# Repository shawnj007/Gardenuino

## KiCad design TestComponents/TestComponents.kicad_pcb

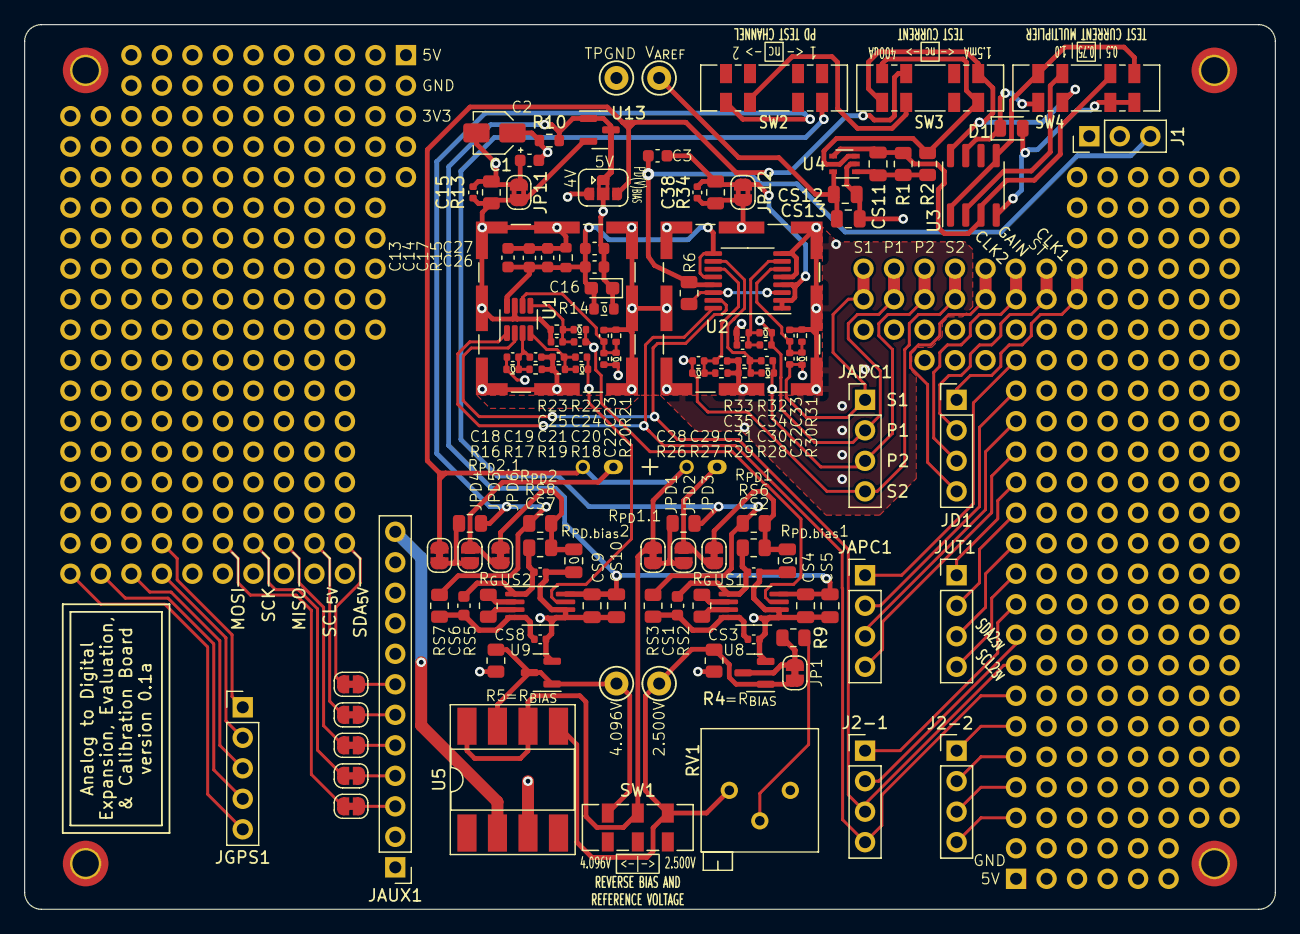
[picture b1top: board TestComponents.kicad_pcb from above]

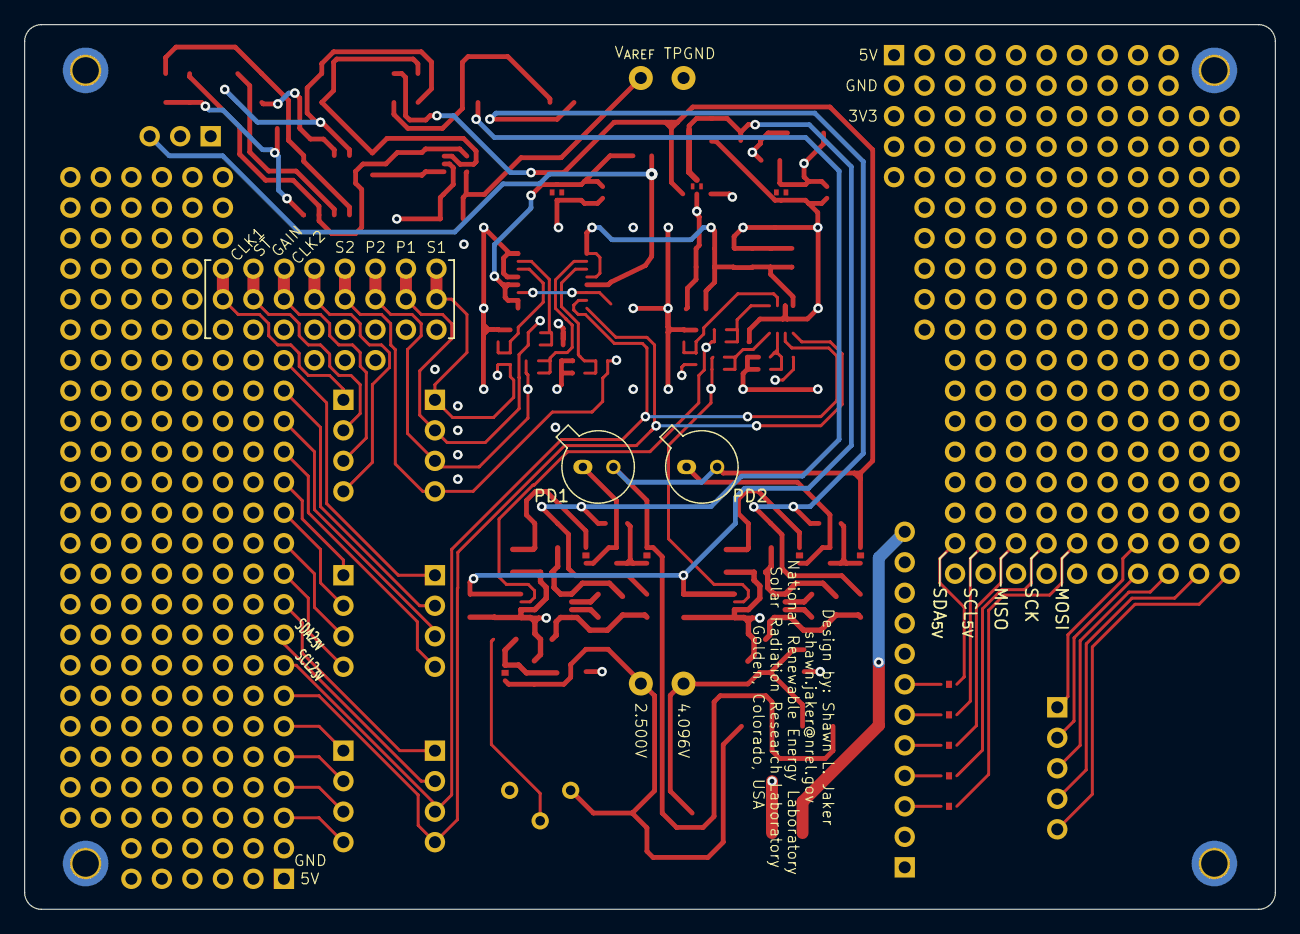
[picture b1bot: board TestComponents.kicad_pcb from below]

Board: 4 copper layers, 104.1 x 73.7 mm, 133 parts (2 on the bottom side), 86 nets.

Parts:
B1: Conn_02x20_Top_Bottom; PinHeader_CornerB1
B2: Conn_02x20_Top_Bottom; PinHeader_CornerB2
C1, C3, C14, C27: 0.1uF; C_0603_1608Metric
C2: 10uF; CP_Elec_3x5.4
C13: 10uF; C_0603_1608Metric
C15, C38: 2.5pF; C_0402_1005Metric
C16: X; CP_EIA-2012-15_AVX-P
C17: X; C_0603_1608Metric
C18, C19, C20, C21, C22, C23, C24, C25, C28, C29, C30, C31, C32, C33, C34, C35: X; C_0402_1005Metric
C26: 1pF; C_0603_1608Metric
CS1, CS6: 11.1pF; C_0603_1608Metric
CS2, CS3, CS7, CS8: 1.11pF; C_0402_1005Metric
CS4, CS9, CS12: 10uF; C_0805_2012Metric
CS5, CS10, CS11, CS13: 0.1uF; C_0805_2012Metric
D1: D_Small; D_0805_2012Metric
H1, H2, H3, H4: MountingHole; MountingHole_2.2mm_M2_ISO14580_Pad_TopBottom
J1: Conn_01x03_Socket; PinHeader_1x03_P2.54mm_Vertical
J2-1, J2-2: Conn_01x04_Male; PinHeader_1x04_P2.54mm_Vertical
J5, J6: RFShield_OnePiece; Laird_Technologies_BMI-S-101_13.66x12.70mm
JADC1: Conn_01x04_Male; PinHeader_1x04_P2.54mm_Vertical
JAPC1: Conn_01x04_Male; PinHeader_1x04_P2.54mm_Vertical
JAUX1: AUX; PinHeader_1x12_P2.54mm_Vertical
JD1: Conn_01x04_Male; PinHeader_1x04_P2.54mm_Vertical
JGPS1: GPS; PinHeader_1x05_P2.54mm_Vertical
JMISO5: SolderJumper_2_Bridged; SolderJumper-2_P1.3mm_Bridged_RoundedPad1.0x1.5mm
JMOSI5: SolderJumper_2_Bridged; SolderJumper-2_P1.3mm_Bridged_RoundedPad1.0x1.5mm
JP1: SolderJumper_2_Bridged; SolderJumper-2_P1.3mm_Bridged_RoundedPad1.0x1.5mm
JP11, JP12: SolderJumper_2_Bridged; SolderJumper-2_P1.3mm_Bridged2Bar_RoundedPad1.0x1.5mm
JP16: SolderJumper_3_Bridged12; SolderJumper-4_P1.3mm_Bridged2Bar12_RoundedPad
JPD1, JPD3, JPD4, JPD6: SolderJumper_2_Bridged; SolderJumper-2_P1.3mm_Bridged_RoundedPad1.0x1.5mm
JPD2, JPD5: SolderJumper_2_Open; SolderJumper-2_P1.3mm_Open_RoundedPad1.0x1.5mm
JSCK5: SolderJumper_2_Bridged; SolderJumper-2_P1.3mm_Bridged_RoundedPad1.0x1.5mm
JSCL5: SolderJumper_2_Bridged; SolderJumper-2_P1.3mm_Bridged_RoundedPad1.0x1.5mm
JSDA5: SolderJumper_2_Bridged; SolderJumper-2_P1.3mm_Bridged_RoundedPad1.0x1.5mm
JUT1: Conn_01x04_Male; PinHeader_1x04_P2.54mm_Vertical
PD1, PD2: S1336-18BK; S1336
R1, R6: 10K; R_0805_2012Metric
R2: 2K67; R_0805_2012Metric
R4: 250; R_0805_2012Metric
R5: 91; R_0805_2012Metric
R9: 470K; R_0805_2012Metric
R10: 24R9; R_0603_1608Metric
R13, R34: 2K; R_0805_2012Metric
R14: 0; R_0603_1608Metric
R15: X; R_0603_1608Metric
R16, R18, R20, R22, R26, R28, R30, R32: 0; R_0402_1005Metric
R17, R19, R21, R23, R27, R29, R31, R33: X; R_0402_1005Metric
RS2, RS5: R_{G}; R_0805_2012Metric
RS3, RS6, RS7, RS8: 330; R_0805_2012Metric
RV1: 10K; Potentiometer_Bourns_3296P_Horizontal
R_{PD.bias}1, R_{PD.bias}2: 1K; C_0805_2012Metric
R_{PD}1, R_{PD}2: 1G; R_0805_2012Metric
R_{PD}1.1, R_{PD}2.1: 1K; R_0805_2012Metric
SW1: SW_DPDT; SW_DPDT_CK_JS202011JAQN
SW2, SW3, SW4: SW_DP3T; SW_DP3T_CK_JS203011JAQN
TPGND-1: TestPoint; TestPoint_Keystone_5000-5004_Miniature
TPV1, TPV2, TPV5: TestPoint; TestPoint_Keystone_5000-5004_Miniature
U1: AD7991; SOT-23-8
U2: ADS1219; TSSOP-16_4.4x5mm_P0.65mm
U3: REF200AU; SOIC-8_3.9x4.9mm_P1.27mm
U4: MCP6L01x-xLT; SOT-353_SC-70-5
U5: LCC110; DIP-8_W8.89mm_SMDSocket_LongPads
U8: ADR5041B; SOT-23
U9: ADR5044B; SOT-23
U13: ADR5045B; SOT-23
US1, US2: AD8221; MSOP-8_3x3mm_P0.65mm

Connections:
2V5: JP1.2 (B), R4.2, RV1.1, SW1.3 (C), TPV1.1, U5.5, U8.1 (K)
3V1: B2.104, C3.2, J1.3, R6.2, U2.13 (DVDD)
4V0: JP16.3 (B), R5.2, SW1.1 (A), TPV2.1, U5.7, U9.1 (K), U9.3 (REF)
5V0: CS4.1, CS5.2, CS9.1, CS10.2, JP16.4, R10.1, U13.1 (K), U13.3 (REF), US1.8 (Vs+), US2.8 (Vs+)
5V3: B1.1, B2.1, C1.1, C2.1, J1.1, JAUX1.1, R4.1, R5.1, R10.2
-I_{const}=0.4mA: SW3.4, SW3.5, SW4.3, U3.8
-I_{const}=1.5mA: R2.1, SW3.1, SW3.8, U4.3 (+)
/InsturmentationsAmps/INV1: JPD3.2 (B), RS6.1, R_{PD.bias}1.1, R_{PD}1.2
/InsturmentationsAmps/INV2: JPD6.2 (B), RS8.1, R_{PD.bias}2.1, R_{PD}2.2
/InsturmentationsAmps/I_{C}1: D1.1 (K), SW4.4, U3.7
/InsturmentationsAmps/I_{C}1out: SW4.7, U3.2
/InsturmentationsAmps/I_{C}in: SW4.5, SW4.8, U3.1, U3.5
/InsturmentationsAmps/I_{C}out: CS11.2, R1.1, SW4.6, U3.3, U4.4 (-)
/InsturmentationsAmps/I_{Mirror}_{IN}: D1.2 (A), SW4.1, SW4.2, U3.4
/InsturmentationsAmps/PD1_{TEST}: RS3.1, R_{PD}1.1, R_{PD}1.1.2, SW2.1
/InsturmentationsAmps/PD2_{TEST}: RS7.1, R_{PD}2.1, R_{PD}2.1.2, SW2.4
/InsturmentationsAmps/PD_{TEST}: SW2.3, SW3.3
/TestConnectors/APCRX_5V: B1.125, JAPC1.2
/TestConnectors/APCTX_5V: B1.136, JAPC1.1
/TestConnectors/CAN_H_5V: B1.85, JUT1.3
/TestConnectors/CAN_L_5V: B1.77, JUT1.4
/TestConnectors/CLK1_5V: B1.164, B1.177, JD1.1
/TestConnectors/CLK2_5V: B1.161, B1.174, JD1.4
/TestConnectors/GAIN_5V: B1.162, B1.175, JD1.3
/TestConnectors/GPSRX_5V: B2.202, JGPS1.3
/TestConnectors/GPSTX_5V: B2.203, JGPS1.4
/TestConnectors/GPS_5V: B2.191, JGPS1.1
/TestConnectors/GPS_GND: B2.201, JGPS1.2
/TestConnectors/MISO_5V: JAUX1.5, JMISO5.1 (A)
/TestConnectors/MOSI_5V: JAUX1.3, JMOSI5.1 (A)
/TestConnectors/PPS_5V: B2.204, JGPS1.5
/TestConnectors/RX_5V: B1.109, JAPC1.4
/TestConnectors/SCK_5V: JAUX1.4, JSCK5.1 (A)
/TestConnectors/SCL_5V: JAUX1.6, JSCL5.1 (A)
/TestConnectors/SDA_5V: JAUX1.7, JSDA5.1 (A)
/TestConnectors/ST_5V: B1.163, B1.176, JD1.2
/TestConnectors/TX_5V: B1.117, JAPC1.3
/TestConnectors/UT1_5V: B1.101, JUT1.1
/TestConnectors/UT2_5V: B1.93, JUT1.2
GND1: B1.7, B1.199, B2.11, C1.2, C2.2, C3.1, C15.2, C38.2, CS2.2, CS3.2, CS4.2, CS5.1, CS7.2, CS8.2, CS9.2, CS10.1, CS12.2, CS13.1, JAUX1.2, JP11.1 (A), JP12.1 (A), R13.2, R34.2, RV1.3, R_{PD.bias}1.2, R_{PD.bias}2.2, TPGND-1.1, U2.1 (A0), U2.2 (A1), U2.4 (DGND), U4.2 (V-), U5.3, U8.2 (A), U9.2 (A), US1.5 (Vs-), US1.6 (Ref), US2.5 (Vs-), US2.6 (Ref)
GND_{RF}: C13.2, C14.2, C15.1, C17.2, C19.2, C21.2, C23.2, C25.2, C29.2, C31.2, C33.2, C35.2, C38.1, J5.1 (Shield), J6.1 (Shield), JP11.2 (B), JP12.2 (B), R13.1, R15.1, R17.1, R19.1, R21.1, R23.1, R27.1, R29.1, R31.1, R33.1, R34.1, U1.7 (GND), U2.5 (AGND), U2.8 (REFN), U13.2 (A)
J-1-1: B1.69, J2-1.1
J-1-2: B1.61, J2-1.2
J-1-3: B1.53, J2-1.3, U1.2 (SDA), U2.15 (SDA)
J-1-4: B1.45, J2-1.4, U1.1 (SCL), U2.16 (SCL)
J-2-1: B1.37, J2-2.1
J-2-2: B1.29, J2-2.2
J-2-3: B1.21, J2-2.3
J-2-4: B1.13, J2-2.4
unnamed: B2.185, JSDA5.2 (B)
unnamed: B2.186, JSCL5.2 (B)
unnamed: B2.187, JMISO5.2 (B)
unnamed: B2.188, JSCK5.2 (B)
unnamed: B2.189, JMOSI5.2 (B)
unnamed: CS11.1, R1.2, R2.2, U4.1
unnamed: JP1.1 (A), R9.1, U8.3 (REF)
unnamed: JPD1.2 (B), JPD2.2 (B), R_{PD}1.1.1
unnamed: JPD2.1 (A), JPD3.1 (A), PD1.1 (A)
unnamed: JPD4.2 (B), JPD5.2 (B), R_{PD}2.1.1
unnamed: JPD5.1 (A), JPD6.1 (A), PD2.1 (A)
unnamed: R9.2, RV1.2
unnamed: RS2.1, US1.3 (Rg)
unnamed: RS2.2, US1.2 (Rg)
unnamed: RS5.1, US2.3 (Rg)
unnamed: RS5.2, US2.2 (Rg)
unnamed: R6.1, U2.3 (~RESET), U2.14 (~DRDY)
unnamed: CS1.1, CS3.1, RS3.2, US1.4 (+)
unnamed: CS1.2, CS2.1, RS6.2, US1.1 (-)
unnamed: CS6.1, CS8.1, RS7.2, US2.4 (+)
unnamed: CS6.2, CS7.1, RS8.2, US2.1 (-)
P1: B1.158, B1.171, C24.1, C34.1, JADC1.2, R22.2, R32.2, US1.7
P1_{RF}: C24.2, C25.1, R22.1, R23.2, U1.5 (Vin2)
P1_{RF}-2: C34.2, C35.1, R32.1, R33.2, U2.7 (AIN2)
P2: B1.159, B1.172, C20.1, C30.1, JADC1.3, R18.2, R28.2, US2.7
P2_{RF}: C20.2, C21.1, R18.1, R19.2, U1.4 (Vin1)
P2_{RF}-2: C30.2, C31.1, R28.1, R29.2, U2.10 (AIN1)
PD(V)_{BIAS}: JP16.1 (A), JPD1.1 (A), JPD4.1 (A), PD1.2 (K), PD2.2 (K), SW1.2 (B), SW3.7, U5.6, U5.8
PWM: JAUX1.12, U5.2
S1: B1.157, B1.170, C22.1, C32.1, JADC1.1, R20.2, R30.2
S1_{RF}: C22.2, C23.1, R20.1, R21.2, U1.6 (Vin3)
S1_{RF}-2: C32.2, C33.1, R30.1, R31.2, U2.6 (AIN3)
S2: B1.160, B1.173, C18.1, C28.1, JADC1.4, R16.2, R26.2
S2_{RF}: C18.2, C19.1, R16.1, R17.2, U1.3 (Vin0)
S2_{RF}-2: C28.2, C29.1, R26.1, R27.2, U2.11 (AIN0)
V_{AREF}: C16.1, C26.1, C27.1, CS12.1, CS13.2, JP16.2 (C), R14.1, TPV5.1, U4.5 (V+)
V_{RF}: C13.1, C14.1, C16.2, C17.1, C26.2, C27.2, R14.2, R15.2, U1.8 (VDD), U2.9 (REFP), U2.12 (AVDD)

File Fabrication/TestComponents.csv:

"Source:","/home/sjaker/gits/Gardenuino/TestComponents/TestComponents.kicad_sch"
"Date:","Mon 10 Jul 2023 09:48:05 PM MDT"
"Tool:","Eeschema 6.0.2+dfsg-1"
"Generator:","/home/sjaker/gits/Gardenuino/bom_csv_grouped_by_value_with_fp_and_pn.py"
"Component Count:","105"
"Ref","Qnty","Value","Cmp name","Footprint","Description","Part Number","Vendor"
"C1, C3, C14, C27, ","4","0.1uF","C","Capacitor_SMD:C_0603_1608Metric","Unpolarized capacitor","CL05A104KA5NNNC",""
"C2, ","1","10uF","C_Polarized_Small_US","Capacitor_SMD:CP_Elec_3x5.4","Polarized capacitor, small US symbol","865090368008 ",""
"C13, ","1","10uF","C_Polarized_Small_US","Capacitor_SMD:C_0603_1608Metric","Polarized capacitor, small US symbol","F381A106MMAAH1",""
"C15, C38, ","2","2.5pF","C_Small","Capacitor_SMD:C_0402_1005Metric","Unpolarized capacitor, small symbol","CL05C2R5CB5NNNC",""
"C16, ","1","X","C_Polarized_US","Capacitor_Tantalum_SMD:CP_EIA-2012-15_AVX-P","Polarized capacitor, US symbol","",""
"C17, ","1","X","C","Capacitor_SMD:C_0603_1608Metric","Unpolarized capacitor","",""
"C18, C19, C20, C21, C22, C23, C24, C25, C28, C29, C30, C31, C32, C33, C34, C35, ","16","X","C","Capacitor_SMD:C_0402_1005Metric","Unpolarized capacitor","",""
"C26, ","1","1pF","C","Capacitor_SMD:C_0603_1608Metric","Unpolarized capacitor","CL05A104KA5NNNC",""
"CS1, CS6, ","2","11.1pF","C_Small","Capacitor_SMD:C_0603_1608Metric","Unpolarized capacitor, small symbol","06035J100FBTTR",""
"CS2, CS3, CS7, CS8, ","4","1.11pF","C_Small","Capacitor_SMD:C_0402_1005Metric","Unpolarized capacitor, small symbol","04023J1R1PBSTR",""
"CS4, CS9, CS12, ","3","10uF","C_Small","Capacitor_SMD:C_0805_2012Metric","Unpolarized capacitor, small symbol","CL21A106KACLRNC",""
"CS5, CS10, CS11, CS13, ","4","0.1uF","C_Small","Capacitor_SMD:C_0805_2012Metric","Unpolarized capacitor, small symbol","CL21B104KACNNNC",""
"J2-1, J2-2, ","2","Conn_01x04_Male","Conn_01x04_Male","Connector_PinHeader_2.54mm:PinHeader_1x04_P2.54mm_Vertical","Generic connector, single row, 01x04, script generated (kicad-library-utils/schlib/autogen/connector/)","PH1-04-UA",""
"J3V1, ","1","Conn_01x01_Male","Conn_01x01_Male","Connector_PinHeader_2.54mm:PinHeader_1x01_P2.54mm_Vertical","Generic connector, single row, 01x01, script generated (kicad-library-utils/schlib/autogen/connector/)","PH1-01-UA",""
"J5, J6, ","2","RFShield_OnePiece","RFShield_OnePiece_2","RF_Shielding:Laird_Technologies_BMI-S-101_13.66x12.70mm","One-piece EMI RF shielding cabinet","BMI-S-101",""
"JADC1, ","1","Conn_01x04_Male","Conn_01x04_Male","Connector_PinHeader_2.54mm:PinHeader_1x04_P2.54mm_Vertical","Generic connector, single row, 01x04, script generated (kicad-library-utils/schlib/autogen/connector/)","PH1-04-UA",""
"JAPC1, ","1","Conn_01x04_Male","Conn_01x04_Male","Connector_PinHeader_2.54mm:PinHeader_1x04_P2.54mm_Vertical","Generic connector, single row, 01x04, script generated (kicad-library-utils/schlib/autogen/connector/)","PH1-04-UA",""
"JAUX1, ","1","AUX","Conn_01x12_Male","Connector_PinHeader_2.54mm:PinHeader_1x12_P2.54mm_Vertical","Generic connector, single row, 01x12, script generated (kicad-library-utils/schlib/autogen/connector/)","PH1-12-UA",""
"JD1, ","1","Conn_01x04_Male","Conn_01x04_Male","Connector_PinHeader_2.54mm:PinHeader_1x04_P2.54mm_Vertical","Generic connector, single row, 01x04, script generated (kicad-library-utils/schlib/autogen/connector/)","PH1-04-UA",""
"JGPS1, ","1","GPS","Conn_01x05_Male","Connector_PinHeader_2.54mm:PinHeader_1x05_P2.54mm_Vertical","Generic connector, single row, 01x05, script generated (kicad-library-utils/schlib/autogen/connector/)","PH1-05-UA",""
"JUT1, ","1","Conn_01x04_Male","Conn_01x04_Male","Connector_PinHeader_2.54mm:PinHeader_1x04_P2.54mm_Vertical","Generic connector, single row, 01x04, script generated (kicad-library-utils/schlib/autogen/connector/)","PH1-04-UA",""
"JVIN1, ","1","Conn_01x01_Male","Conn_01x01_Male","Connector_PinHeader_2.54mm:PinHeader_1x01_P2.54mm_Vertical","Generic connector, single row, 01x01, script generated (kicad-library-utils/schlib/autogen/connector/)","PH1-01-UA",""
"R1, R6, ","2","10K","R","Resistor_SMD:R_0805_2012Metric","Resistor","ERA-6VRW1002V",""
"R2, ","1","2K67","R","Resistor_SMD:R_0805_2012Metric","Resistor","ERJ-PB6B2671V",""
"R4, ","1","402","R","Resistor_SMD:R_0805_2012Metric","Resistor","ERJ-PB6B4020V",""
"R5, ","1","200","R","Resistor_SMD:R_0805_2012Metric","Resistor","ERJ-6ENF1740V",""
"R9, ","1","470K","R","Resistor_SMD:R_0805_2012Metric","Resistor","ERJ-PB6B4703V",""
"R10, R15, ","2","X","R","Resistor_SMD:R_0603_1608Metric","Resistor","",""
"R13, R34, ","2","2K","R","Resistor_SMD:R_0805_2012Metric","Resistor","ERJ-6ENF2001V",""
"R14, ","1","0","R","Resistor_SMD:R_0603_1608Metric","Resistor","ERJ-U030R00V",""
"R16, R18, R20, R22, R26, R28, R30, R32, ","8","0","R","Resistor_SMD:R_0402_1005Metric","Resistor","ERJ-2GE0R00X",""
"R17, R19, R21, R23, R27, R29, R31, R33, ","8","X","R","Resistor_SMD:R_0402_1005Metric","Resistor","",""
"R_{C}1, ","1","500","R","Resistor_SMD:R_0805_2012Metric","Resistor","ERJ-PB6B4990V",""
"R_{PD.bias}1, R_{PD.bias}2, ","2","0","R","Capacitor_SMD:C_0805_2012Metric","Resistor","ERJ-6GEY0R00V",""
"R_{PD}1, R_{PD}2, ","2","1M","R","Resistor_SMD:R_0805_2012Metric","Resistor","ERA-6AEB105V",""
"R_{PD}1.1, ","1","2K","R","Resistor_SMD:R_0805_2012Metric","Resistor","ERJ-6ENF2001V",""
"R_{PD}2.1, ","1","2K","R","Resistor_SMD:R_0805_2012Metric","Resistor","ERJ-6ENF2001V",""
"RS2, RS5, ","2","R_{G}","R","Capacitor_SMD:C_0805_2012Metric","Resistor","",""
"RS3, RS6, RS7, RS8, ","4","330","R","Resistor_SMD:R_0805_2012Metric","Resistor","ERA-6VEB3300V",""
"RV1, ","1","10K","R_Potentiometer","Potentiometer_THT:Potentiometer_Bourns_3296P_Horizontal","Potentiometer","3296P-1-103LF",""
"SW1, SW3, ","2","SW_DPDT","SW_DPDT_x2","Gardenuino Custom:SW_DPDT_CK_JS202011JAQN","Switch, dual pole double throw, separate symbols","JS202011JAQN",""
"SW2, ","1","SW_DP3T","SW_DP3T","Gardenuino Custom:SW_DP3T_CK_JS203011JAQN","Switch, three position, dual pole triple throw, 3 position switch, SP3T","JS203011JAQN",""
"U1, ","1","AD7991","AD799x","Package_TO_SOT_SMD:SOT-23-8","","AD7991YRJZ-1500RL7",""
"U2, ","1","ADS1219","ADS1219","Package_SO:TSSOP-16_4.4x5mm_P0.65mm","Low-power, quad-input, 24-bit analog to digital converter, integrated temperature sensor, SPI interface, TSSOP-16 package","ADS1219",""
"U3, ","1","REF200AU","REF200AU","Package_SO:SOIC-8_3.9x4.9mm_P1.27mm","2x100μA Current Sources/Sinks with Current Mirror, SO-8","REF200AU",""
"U4, ","1","MCP6L01x-xLT","MCP6L01x-xLT","Package_TO_SOT_SMD:SOT-353_SC-70-5","Single, 1 MHz, Rail-to-Rail input and output, SC-70-5","MCP6L01T-E/LT",""
"U8, ","1","ADR510","ADR510_1","Package_TO_SOT_SMD:SOT-23","Shunt Regulator, SOT-23","ADR510ARTZ-REEL7",""
"U9, ","1","ADR5043BRTZ","ADR510","Package_TO_SOT_SMD:SOT-23","Shunt Regulator, SOT-23","ADR5043BRTZ",""
"U13, ","1","X","ADR510","Package_TO_SOT_SMD:SOT-23","Shunt Regulator, SOT-23","",""
"US1, US2, ","2","AD8221","AD8236","Package_SO:MSOP-8_3x3mm_P0.65mm","Single 40 μA Micropower Instrumentation Amplifier with Zero Crossover Distortion, MSOP-8","AD8221ARMZ",""

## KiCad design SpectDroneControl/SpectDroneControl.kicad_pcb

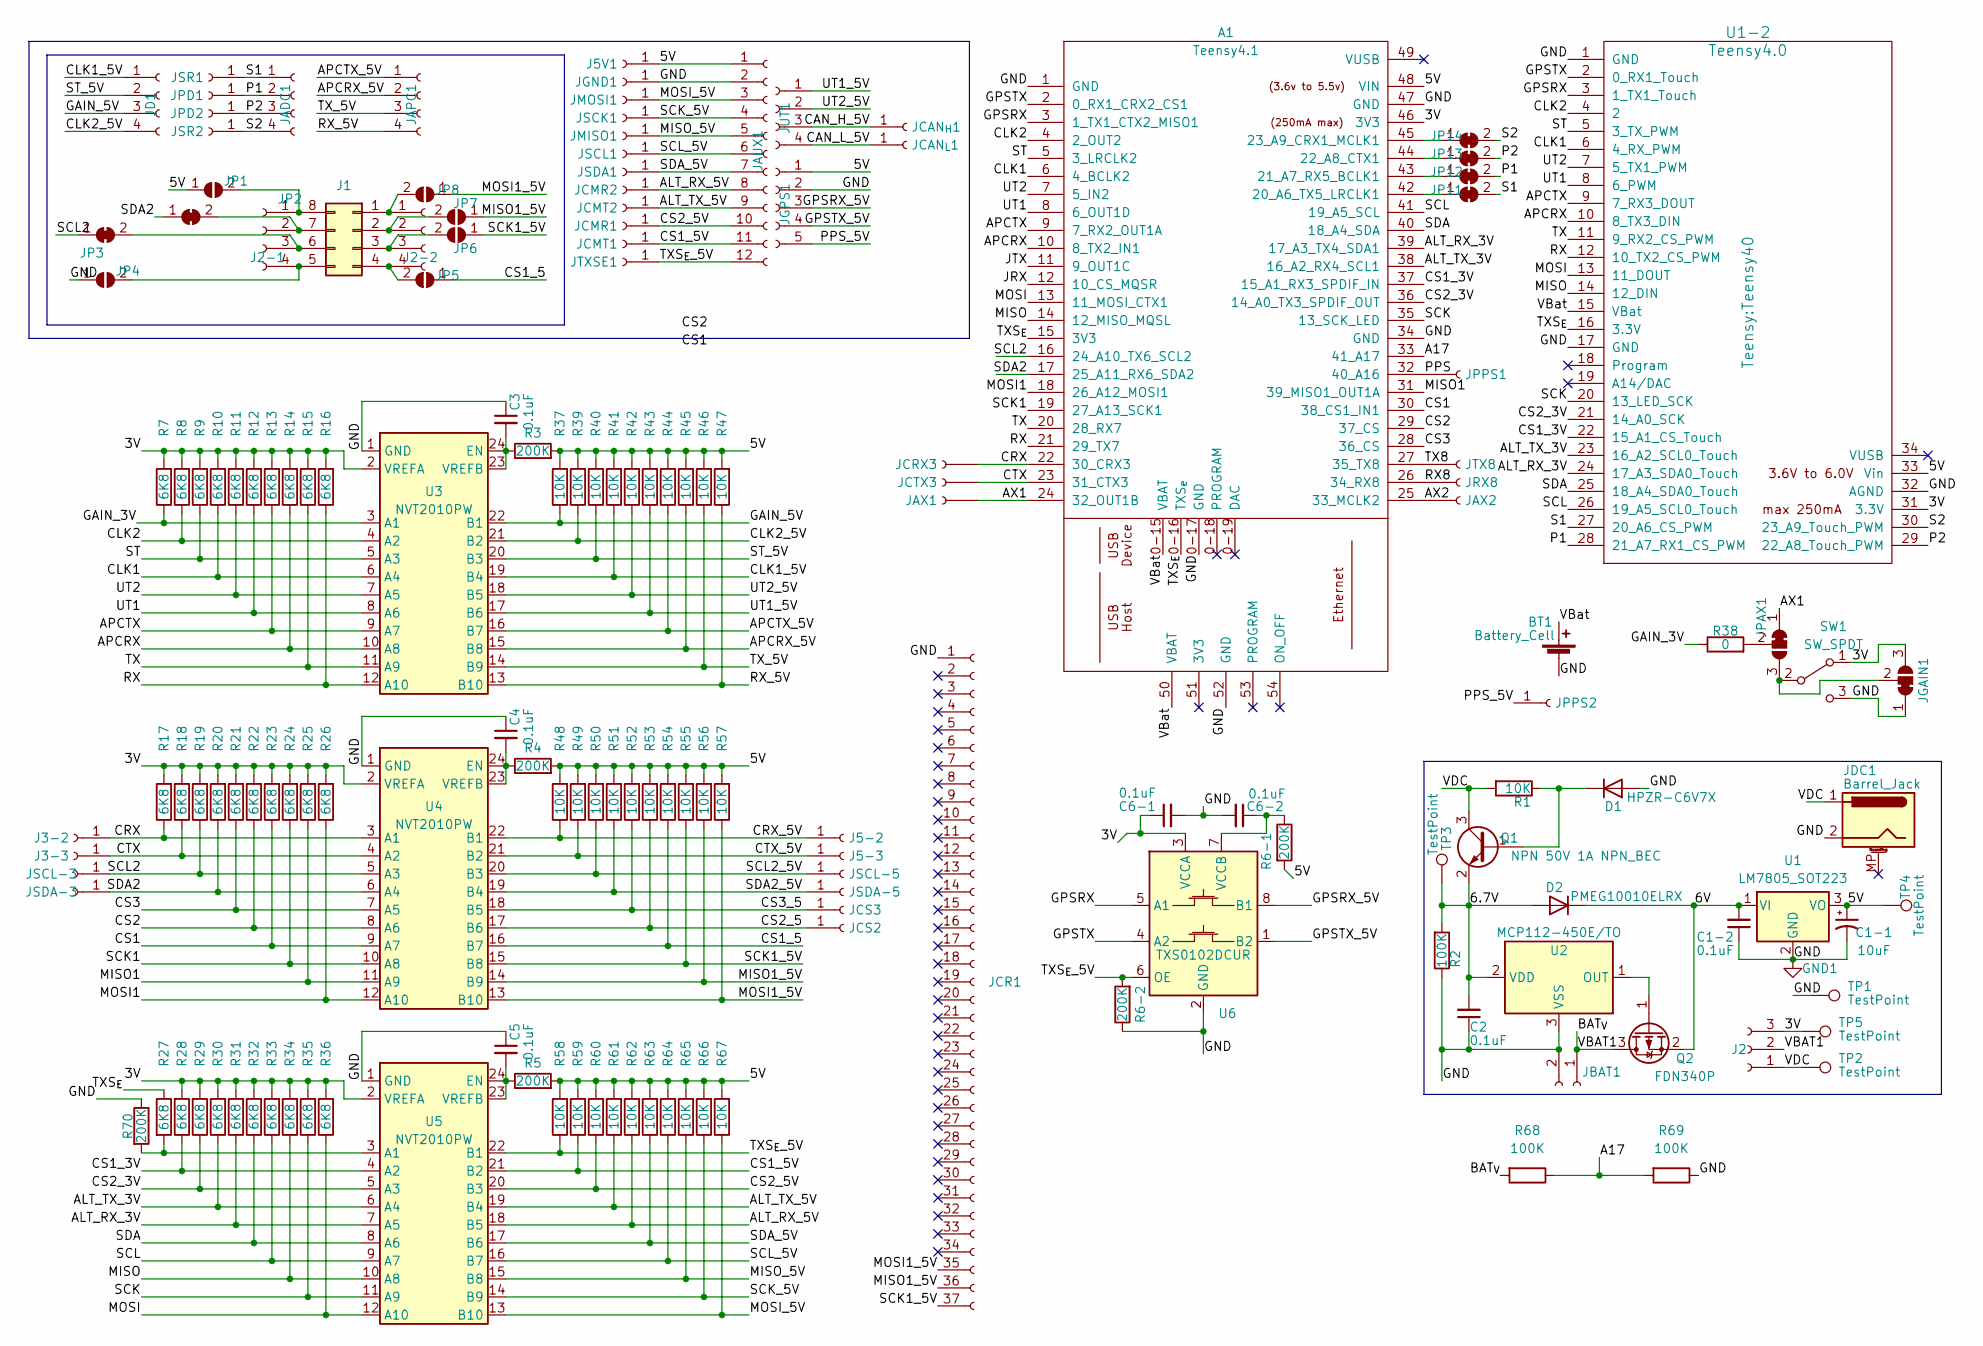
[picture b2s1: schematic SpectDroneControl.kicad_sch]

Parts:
A1: Teensy4.1; Teensy4.0-1
BT1: Battery_Cell; BatteryHolder_Keystone_3000_1x12mm; Part Number 3000
C1-1: 10uF; CP_Elec_3x5.4; Part Number 865090368008
C1-2, C2, C3, C4, C5, C6-1, C6-2: 0.1uF; C_0805_2012Metric; Part Number CL21B104KACNNNC
D1: D; D_SOD-123F; Part Number HPZR-C6V7X
D2: D; Nexperia_CFP3_SOD-123W; Part Number PMEG10010ELRX
J1: Conn_02x03_Counter_Clockwise; PinSocket_2x04_P2.54mm_Vertical_renumber; Part Number RS2-08-G
J2: Conn_01x03_Socket; PinSocket_1x03_P2.54mm_Vertical
J2-1, J2-2: Conn_01x04_Female; PinSocket_1x04_P2.54mm_Vertical; Part Number PH1-04-UA
J3-2, J3-3: Conn_01x01_Female; SolderWire-0.1sqmm_1x01_D0.4mm_OD1mm; Part Number RS1-01G
J5-2, J5-3, J5V1: Conn_01x01_Female; SolderWire-0.1sqmm_1x01_D0.4mm_OD1mm
JADC1: Conn_01x04_Female; PinSocket_1x04_P2.54mm_Vertical; Part Number PH1-04-UA
JAPC1: Conn_01x04_Female; PinSocket_1x04_P2.54mm_Vertical; Part Number PH1-04-UA
JAUX1: AUX; PinSocket_1x12_P2.54mm_Vertical; Part Number RS1-12-G
JAX1, JAX2: Conn_01x01_Female; SolderWire-0.1sqmm_1x01_D0.4mm_OD1mm
JBAT1: Conn_01x02_Female; Molex_Micro-Fit_3.0_43045-0200_2x01_P3.00mm_Horizontal
JCAN_{H}1: Conn_01x01_Female; SolderWire-0.1sqmm_1x01_D0.4mm_OD1mm
JCAN_{L}1: Conn_01x01_Female; SolderWire-0.1sqmm_1x01_D0.4mm_OD1mm
JCMR1, JCMR2: Conn_01x01_Female; SolderWire-0.1sqmm_1x01_D0.4mm_OD1mm
JCMT1, JCMT2: Conn_01x01_Female; SolderWire-0.1sqmm_1x01_D0.4mm_OD1mm
JCR1: Conn_01x37_Female; PinHeader_Corner
JCRX3: Conn_01x01_Female; SolderWire-0.1sqmm_1x01_D0.4mm_OD1mm
JCS2, JCS3: Conn_01x01_Female; SolderWire-0.1sqmm_1x01_D0.4mm_OD1mm
JCTX3: Conn_01x01_Female; SolderWire-0.1sqmm_1x01_D0.4mm_OD1mm
JD1: Conn_01x04_Female; PinSocket_1x04_P2.54mm_Vertical; Part Number PH1-04-UA
JDC1: Barrel_Jack; BarrelJack_CUI_PJ-063AH_Horizontal
JGAIN1: SolderJumper; SolderJumper-3_P1.3mm_Bridged12_RoundedPad1.0x1.5mm
JGND1: Conn_01x01_Female; SolderWire-0.1sqmm_1x01_D0.4mm_OD1mm
JGPS1: GPS; PinSocket_1x05_P2.54mm_Vertical; Part Number PH1-05-UA
JMISO1: Conn_01x01_Female; SolderWire-0.1sqmm_1x01_D0.4mm_OD1mm
JMOSI1: Conn_01x01_Female; SolderWire-0.1sqmm_1x01_D0.4mm_OD1mm
JP1, JP4, JP5, JP6, JP7, JP8: SolderJumper_2_Open; SolderJumper-2_P1.3mm_Open_RoundedPad1.0x1.5mm
JP2, JP3: SolderJumper_2_Open; SolderJumper-2_P1.3mm_Bridged_RoundedPad1.0x1.5mm
JP11, JP12, JP13, JP14: SolderJumper_2_Bridged; SolderJumper-2_P1.3mm_Bridged_RoundedPad1.0x1.5mm
JPAX1: SolderJumper; SolderJumper-3_P1.3mm_Bridged12_RoundedPad1.0x1.5mm
JPD1, JPD2: Conn_01x01_Female; SolderWire-0.1sqmm_1x01_D0.4mm_OD1mm
JPPS1, JPPS2: Conn_01x01_Female; SolderWire-0.1sqmm_1x01_D0.4mm_OD1mm
JRX8: Conn_01x01_Female; SolderWire-0.1sqmm_1x01_D0.4mm_OD1mm
JSCK1: Conn_01x01_Female; SolderWire-0.1sqmm_1x01_D0.4mm_OD1mm
JSCL1: Conn_01x01_Female; SolderWire-0.1sqmm_1x01_D0.4mm_OD1mm
JSCL-3: Conn_01x01_Female; SolderWire-0.1sqmm_1x01_D0.4mm_OD1mm; Part Number RS1-01G
JSCL-5: Conn_01x01_Female; SolderWire-0.1sqmm_1x01_D0.4mm_OD1mm
JSDA1: Conn_01x01_Female; SolderWire-0.1sqmm_1x01_D0.4mm_OD1mm
JSDA-3: Conn_01x01_Female; SolderWire-0.1sqmm_1x01_D0.4mm_OD1mm; Part Number RS1-01G
JSDA-5: Conn_01x01_Female; SolderWire-0.1sqmm_1x01_D0.4mm_OD1mm
JSR1, JSR2: Conn_01x01_Female; SolderWire-0.1sqmm_1x01_D0.4mm_OD1mm
JTX8: Conn_01x01_Female; SolderWire-0.1sqmm_1x01_D0.4mm_OD1mm
JTXSE1: Conn_01x01_Female; SolderWire-0.1sqmm_1x01_D0.4mm_OD1mm
JUT1: Conn_01x04_Female; PinSocket_1x04_P2.54mm_Vertical; Part Number PH1-04-UA
Q1: NPN 50V 1A NPN_BEC; SOT-323_SC-70; Part Number ZUMT618
Q2: FDN340P; SOT-23; Part Number FDN340P
R1: 10K; R_0805_2012Metric; Part Number ERJ-6ENF1001V
R2: 100K; R_0805_2012Metric; Part Number ERJ-6ENF1003V
R3, R4, R5, R6-1, R6-2, R70: 200K; R_0805_2012Metric; Part Number ERJ-6ENF2003V
R7, R8, R9, R10, R11, R12, R13, R14, R15, R16, R17, R18, R19, R20, R21, R22, R23, R24, R25, R26, R27, R28, R29, R30, R31, R32, R33, R34, R35, R36: 6K8; R_0805_2012Metric; Part Number ERJ-6ENF6801V
R37, R39, R40, R41, R42, R43, R44, R45, R46, R47, R48, R49, R50, R51, R52, R53, R54, R55, R56, R57, R58, R59, R60, R61, R62, R63, R64, R65, R66, R67: 10K; R_0805_2012Metric; Part Number ERJ-6ENF1002V
R38: 0; R_0805_2012Metric; Part Number ERJ-6ENF1002V
R68, R69: 100K; R_0805_2012Metric
SW1: SW_SPDT; SW_SPDT_CK-JS102011SAQN; Part Number JS102011SAQN
TP1, TP2, TP3, TP4, TP5: TestPoint; TestPoint_Keystone_5000-5004_Miniature
U1: LM7805_SOT223; SOT-223-3_TabPin2; Part Number LM7805_SOT223
U1-2: Teensy4.0; Teensy40
U2: MCP112-450E/TO; SOT-89-3; Part Number MCP112T-450E/MB
U3, U4, U5: NVT2010PW; TSSOP-24_4.4x7.8mm_P0.65mm; Part Number NVT2010PW
U6: TXS0102DCUR; SSOP-8_2.95x2.8mm_P0.65mm; Part Number TXS0102DCUR

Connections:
/3V: A1.46 (3V3), C6-1.1, J2.3, JGAIN1.3 (B), R7.2, R8.2, R9.2, R10.2, R11.2, R12.2, R13.2, R14.2, R15.2, R16.2, R17.2, R18.2, R19.2, R20.2, R21.2, R22.2, R23.2, R24.2, R25.2, R26.2, R28.2, R29.2, R30.2, R31.2, R32.2, R33.2, R34.2, R35.2, R36.2, SW1.1 (A), TP5.1, U1-2.31 (3.3V), U3.2 (VREFA), U4.2 (VREFA), U5.2 (VREFA), U6.3 (VCCA)
/5V: A1.48 (VIN), C1-1.1, J5V1.1, JAUX1.1, JGPS1.1, JP1.1 (A), R3.2, R4.2, R5.2, R6-1.2, R37.2, R39.2, R40.2, R41.2, R42.2, R43.2, R44.2, R45.2, R46.2, R47.2, R48.2, R49.2, R50.2, R51.2, R52.2, R53.2, R54.2, R55.2, R56.2, R57.2, R58.2, R59.2, R60.2, R61.2, R62.2, R63.2, R64.2, R65.2, R66.2, R67.2, TP4.1, U1.3 (VO), U1-2.33 (Vin)
/6.7V: C2.2, D2.2 (A), Q1.2 (E), R2.2, TP3.1, U2.2 (VDD)
/6V: C1-2.2, D2.1 (K), Q2.2 (S), U1.1 (VI)
/A17: A1.33 (41_A17), R68.1, R69.2
/ALT_RX_3V: A1.39 (17_A3_TX4_SDA1), R31.1, U1-2.24 (17_A3_SDA0_Touch), U5.7 (A5)
/ALT_RX_5V: JAUX1.8, JCMR2.1, R62.1, U5.18 (B5)
/ALT_TX_3V: A1.38 (16_A2_RX4_SCL1), R30.1, U1-2.23 (16_A2_SCL0_Touch), U5.6 (A4)
/ALT_TX_5V: JAUX1.9, JCMT2.1, R61.1, U5.19 (B4)
/APCRX: A1.10 (8_TX2_IN1), R14.1, U1-2.10 (8_TX3_DIN), U3.10 (A8)
/APCRX_5V: JAPC1.2, R45.1, U3.15 (B8)
/APCTX: A1.9 (7_RX2_OUT1A), R13.1, U1-2.9 (7_RX3_DOUT), U3.9 (A7)
/APCTX_5V: JAPC1.1, R44.1, U3.16 (B7)
/AX1: A1.24 (32_OUT1B), JAX1.1, JPAX1.1 (A)
/AX2: A1.25 (33_MCLK2), JAX2.1
/BAT_{V}: J2.2, JBAT1.1, Q2.3 (D), R68.2
/CAN_H_5V: JCAN_{H}1.1, JUT1.3
/CAN_L_5V: JCAN_{L}1.1, JUT1.4
/CLK1: A1.6 (4_BCLK2), R10.1, U1-2.6 (4_RX_PWM), U3.6 (A4)
/CLK1_5V: JD1.1, R41.1, U3.19 (B4)
/CLK2: A1.4 (2_OUT2), R8.1, U1-2.4 (2), U3.4 (A2)
/CLK2_5V: JD1.4, R39.1, U3.21 (B2)
/CRX: A1.22 (30_CRX3), J3-2.1, JCRX3.1, R17.1, U4.3 (A1)
/CRX_5V: J5-2.1, R48.1, U4.22 (B1)
/CS1: A1.30 (38_CS1_IN1), R23.1, U4.9 (A7)
/CS1_3V: A1.37 (15_A1_RX3_SPDIF_IN), R28.1, U1-2.22 (15_A1_CS_Touch), U5.4 (A2)
/CS1_5: JP5.1 (A), R54.1, U4.16 (B7)
/CS1_5V: JAUX1.11, JCMT1.1, R59.1, U5.21 (B2)
/CS2: A1.29 (37_CS), R22.1, U4.8 (A6)
/CS2_3V: A1.36 (14_A0_TX3_SPDIF_OUT), R29.1, U1-2.21 (14_A0_SCK), U5.5 (A3)
/CS2_5: JCS2.1, R53.1, U4.17 (B6)
/CS2_5V: JAUX1.10, JCMR1.1, R60.1, U5.20 (B3)
/CS3: A1.28 (36_CS), R21.1, U4.7 (A5)
/CS3_5: JCS3.1, R52.1, U4.18 (B5)
/CTX: A1.23 (31_CTX3), J3-3.1, JCTX3.1, R18.1, U4.4 (A2)
/CTX_5V: J5-3.1, R49.1, U4.21 (B2)
/GAIN_3V: R7.1, R38.1, U3.3 (A1)
/GAIN_5V: JD1.3, R37.1, U3.22 (B1)
/GPSRX: A1.3 (1_TX1_CTX2_MISO1), U1-2.3 (1_TX1_Touch), U6.5 (A1)
/GPSRX_5V: JGPS1.3, U6.8 (B1)
/GPSTX: A1.2 (0_RX1_CRX2_CS1), U1-2.2 (0_RX1_Touch), U6.4 (A2)
/GPSTX_5V: JGPS1.4, U6.1 (B2)
/JRX: A1.12 (10_CS_MQSR)
/JTX: A1.11 (9_OUT1C)
/MISO: A1.14 (12_MISO_MQSL), R34.1, U1-2.14 (12_DIN), U5.10 (A8)
/MISO1: A1.31 (39_MISO1_OUT1A), R25.1, U4.11 (A9)
/MISO1_5V: JCR1.36, JP7.1 (A), R56.1, U4.14 (B9)
/MISO_5V: JAUX1.5, JMISO1.1, R65.1, U5.15 (B8)
/MOSI: A1.13 (11_MOSI_CTX1), R36.1, U1-2.13 (11_DOUT), U5.12 (A10)
/MOSI1: A1.18 (26_A12_MOSI1), R26.1, U4.12 (A10)
/MOSI1_5V: JCR1.35, JP8.1 (A), R57.1, U4.13 (B10)
/MOSI_5V: JAUX1.3, JMOSI1.1, R67.1, U5.13 (B10)
/P1: JADC1.2, JP12.2 (B), JPD1.1, U1-2.28 (21_A7_RX1_CS_PWM)
/P2: JADC1.3, JP13.2 (B), JPD2.1, U1-2.29 (22_A8_Touch_PWM)
/PPS: A1.32 (40_A16), JPPS1.1
/PPS_5V: JGPS1.5, JPPS2.1
/RX: A1.21 (29_TX7), R16.1, U1-2.12 (10_TX2_CS_PWM), U3.12 (A10)
/RX8: A1.26 (34_RX8), JRX8.1
/RX_5V: JAPC1.4, R47.1, U3.13 (B10)
/S1: JADC1.1, JP11.2 (B), JSR1.1, U1-2.27 (20_A6_CS_PWM)
/S2: JADC1.4, JP14.2 (B), JSR2.1, U1-2.30 (23_A9_Touch_PWM)
/SCK: A1.35 (13_SCK_LED), R35.1, U1-2.20 (13_LED_SCK), U5.11 (A9)
/SCK1: A1.19 (27_A13_SCK1), R24.1, U4.10 (A8)
/SCK1_5V: JCR1.37, JP6.1 (A), R55.1, U4.15 (B8)
/SCK_5V: JAUX1.4, JSCK1.1, R66.1, U5.14 (B9)
/SCL: A1.41 (19_A5_SCL), R33.1, U1-2.26 (19_A5_SCL0_Touch), U5.9 (A7)
/SCL2: A1.16 (24_A10_TX6_SCL2), JP3.1 (A), JSCL-3.1, R19.1, U4.5 (A3)
/SCL2_5V: JSCL-5.1, R50.1, U4.20 (B3)
/SCL_5V: JAUX1.6, JSCL1.1, R64.1, U5.16 (B7)
/SDA: A1.40 (18_A4_SDA), R32.1, U1-2.25 (18_A4_SDA0_Touch), U5.8 (A6)
/SDA2: A1.17 (25_A11_RX6_SDA2), JP2.1 (A), JSDA-3.1, R20.1, U4.6 (A4)
/SDA2_5V: JSDA-5.1, R51.1, U4.19 (B4)
/SDA_5V: JAUX1.7, JSDA1.1, R63.1, U5.17 (B6)
/ST: A1.5 (3_LRCLK2), R9.1, U1-2.5 (3_TX_PWM), U3.5 (A3)
/ST_5V: JD1.2, R40.1, U3.20 (B3)
/TX: A1.20 (28_RX7), R15.1, U1-2.11 (9_RX2_CS_PWM), U3.11 (A9)
/TX8: A1.27 (35_TX8), JTX8.1
/TXS_{E}: A1.0-16 (TXS_{e}), A1.15 (3V3), R27.1, U1-2.16 (3.3V)
/TXS_{E}_5V: JAUX1.12, JTXSE1.1, R6-2.2, R58.1, U5.22 (B1), U6.6 (OE)
/TX_5V: JAPC1.3, R46.1, U3.14 (B9)
/UT1: A1.8 (6_OUT1D), R12.1, U1-2.8 (6_PWM), U3.8 (A6)
/UT1_5V: JUT1.1, R43.1, U3.17 (B6)
/UT2: A1.7 (5_IN2), R11.1, U1-2.7 (5_TX1_PWM), U3.7 (A5)
/UT2_5V: JUT1.2, R42.1, U3.18 (B5)
/VBat: A1.0-15 (VBAT), A1.50 (VBAT), BT1.1 (+), U1-2.15 (VBat)
/VDC: J2.1, JDC1.1, Q1.3 (C), R1.2, TP2.1
GND1: A1.0-17 (GND), A1.1 (GND), A1.34 (GND), A1.47 (GND), A1.52 (GND), BT1.2 (-), C1-1.2, C1-2.1, C2.1, C3.1, C4.1, C5.1, C6-1.2, C6-2.2, D1.2 (A), JAUX1.2, JBAT1.2, JCR1.1, JDC1.2, JGAIN1.1 (A), JGND1.1, JGPS1.2, JP4.1 (A), R2.1, R6-2.1, R69.1, R70.1, SW1.3 (C), TP1.1, U1.2 (GND), U1-2.1 (GND), U1-2.17 (GND), U1-2.32 (AGND), U2.3 (VSS), U3.1 (GND), U4.1 (GND), U5.1 (GND), U6.2 (GND)
unnamed: A1.42 (20_A6_TX5_LRCLK1), JP11.1 (A)
unnamed: A1.43 (21_A7_RX5_BCLK1), JP12.1 (A)
unnamed: A1.44 (22_A8_CTX1), JP13.1 (A)
unnamed: A1.45 (23_A9_CRX1_MCLK1), JP14.1 (A)
unnamed: D1.1 (K), Q1.1 (B), R1.1
unnamed: J1.1, J2-2.1, JP8.2 (B)
unnamed: J1.2, J2-2.2, JP7.2 (B)
unnamed: J1.3, J2-2.3, JP6.2 (B)
unnamed: J1.4, J2-2.4, JP5.2 (B)
unnamed: J1.5, J2-1.4, JP4.2 (B)
unnamed: J1.6, J2-1.3, JP3.2 (B)
unnamed: J1.7, J2-1.2, JP2.2 (B)
unnamed: J1.8, J2-1.1, JP1.2 (B)
unnamed: JGAIN1.2 (C), JPAX1.3 (B), SW1.2 (B)
unnamed: JPAX1.2 (C), R38.2
unnamed: Q2.1 (G), U2.1 (OUT)
unnamed: C3.2, R3.1, U3.23 (VREFB), U3.24 (EN)
unnamed: C4.2, R4.1, U4.23 (VREFB), U4.24 (EN)
unnamed: R27.2, R70.2, U5.3 (A1)
unnamed: C5.2, R5.1, U5.23 (VREFB), U5.24 (EN)
unnamed: C6-2.1, R6-1.1, U6.7 (VCCB)

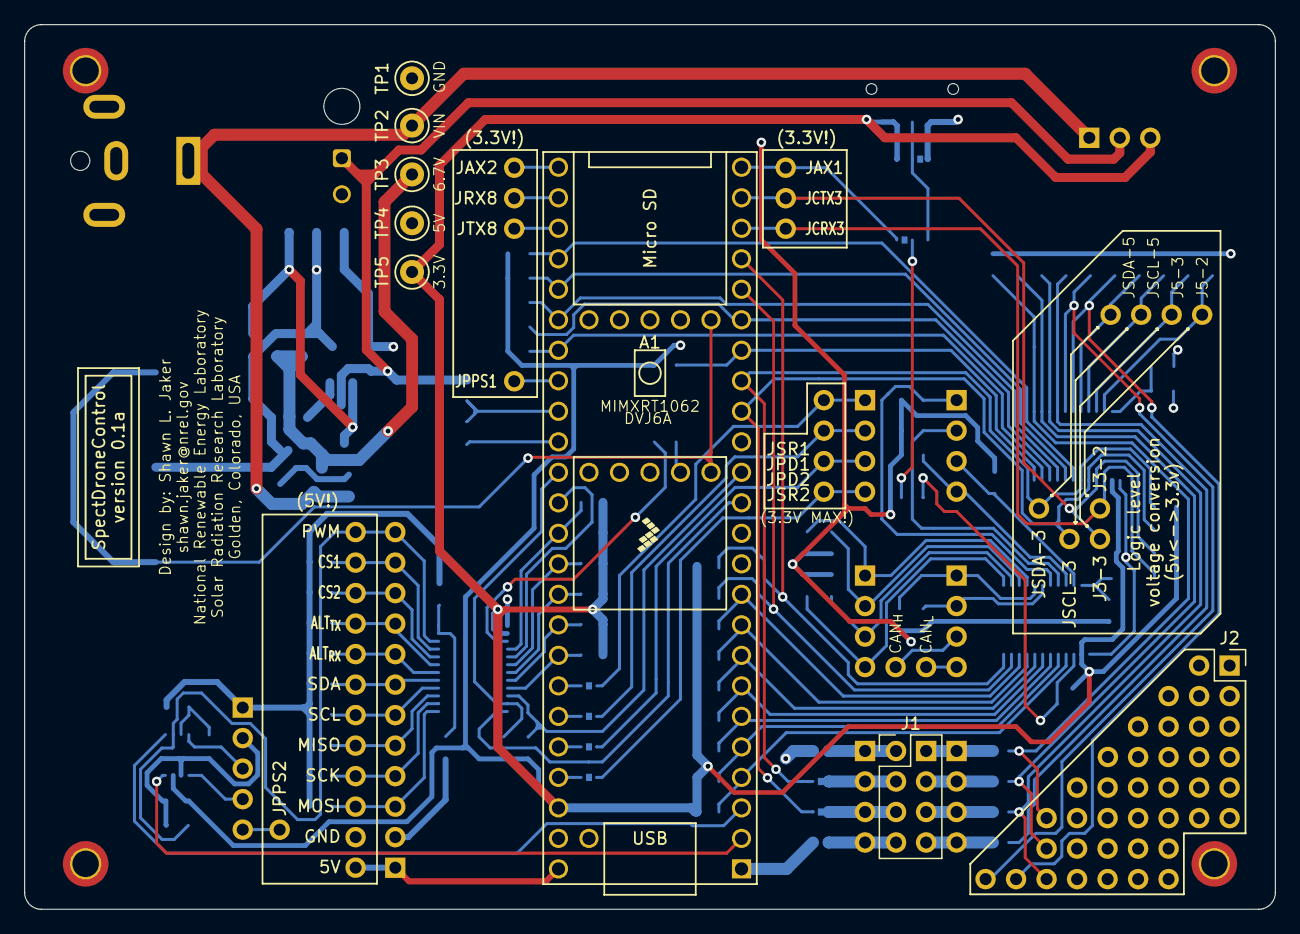
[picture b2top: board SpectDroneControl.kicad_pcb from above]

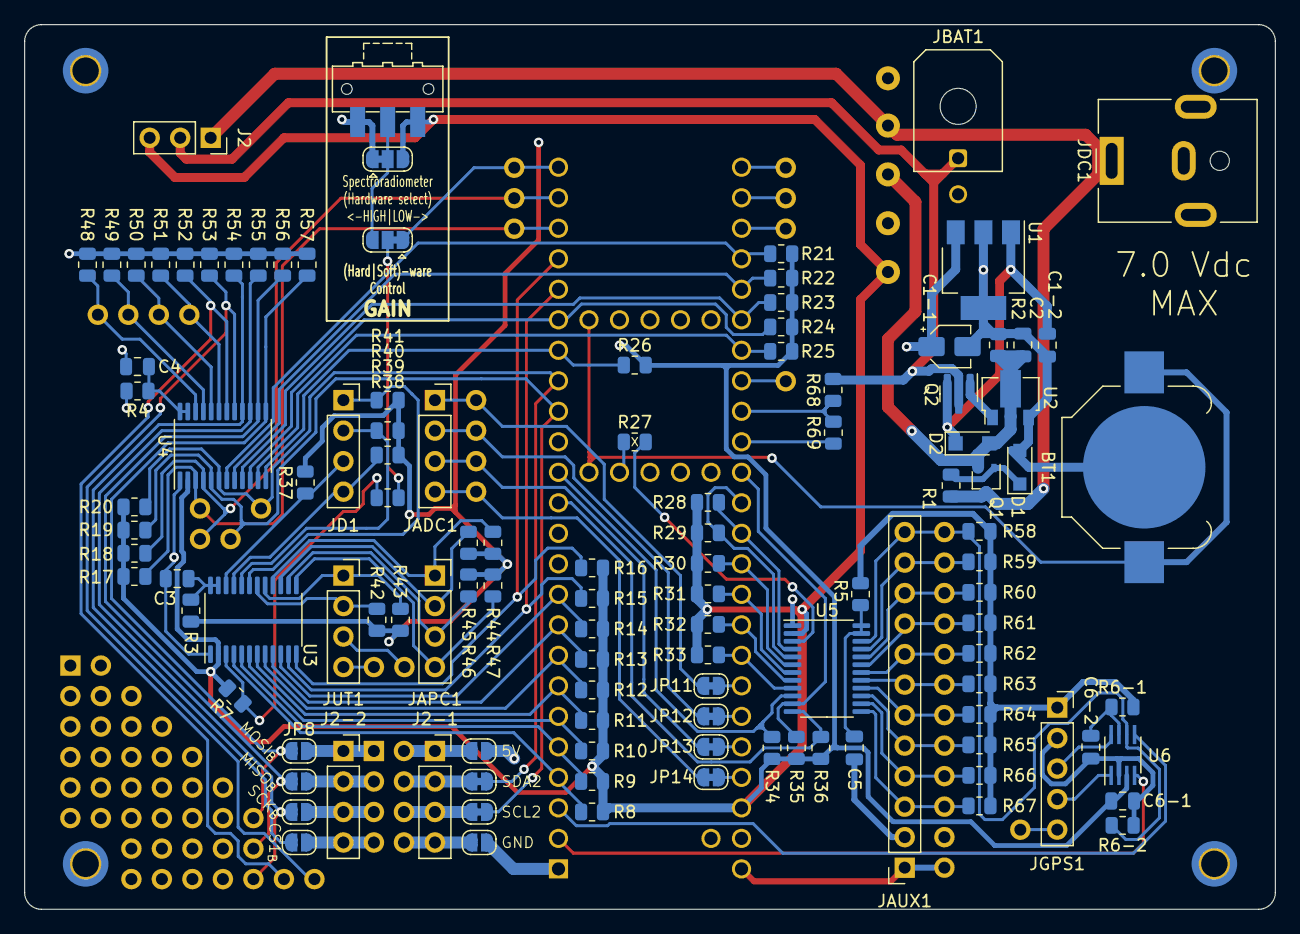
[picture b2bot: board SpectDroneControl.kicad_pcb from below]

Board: 4 copper layers, 104.1 x 73.7 mm, 163 parts (118 on the bottom side), 106 nets.

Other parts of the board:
H1, H2, H3, H4: MountingHole; MountingHole_2.2mm_M2_ISO14580_Pad_TopBottom
